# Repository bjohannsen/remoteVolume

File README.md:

# remoteVolume
An AVR-based IR controlled audio volume controller.
Primary purpose was to use active studio monitors with a TV without a fitting AV receiver.

# Features
* ATmega168 controller
* Volume controlling via <a href="http://www.ti.com/lit/ds/symlink/pga2311.pdf" target="_blank">TI PGA2311</a>
* Working with most IR protocols thanks to <a href="http://www.mikrocontroller.net/articles/IRMP" target="_blank">IRMP</a> library
* Two selectable input sources
* Switch output to control a subwoofer
* Display current volume by a ring of LEDs and a motorized pot.

#Caveats
* External power supply needed, for example <a href="http://www.meanwell.com/search/NET-35/NET-35-spec.pdf" target="_blank">Mean Well NET-35B</a>

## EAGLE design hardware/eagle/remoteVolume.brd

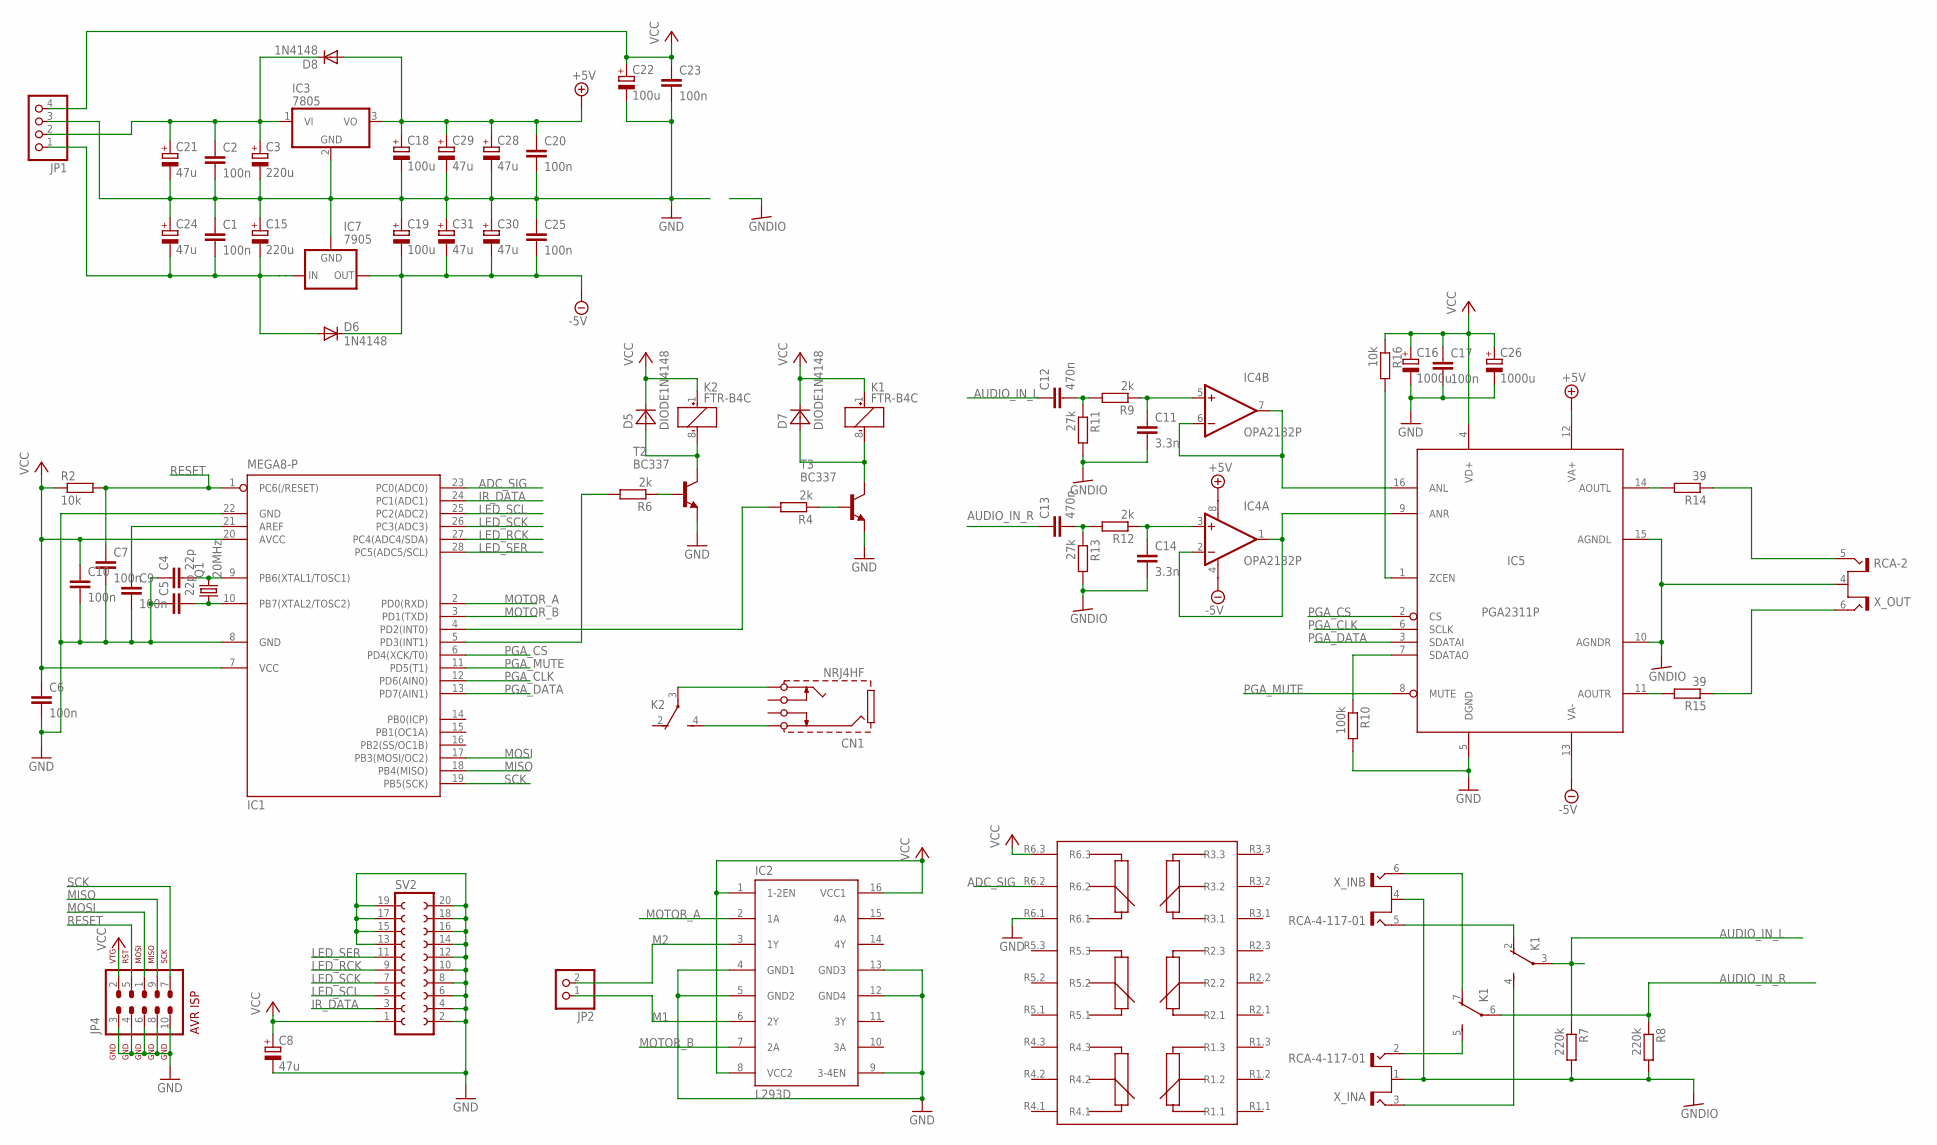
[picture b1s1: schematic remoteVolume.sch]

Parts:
C1, C2, C6, C7, C9, C10, C17, C20, C23, C25: 100n; C025-025X050
C3, C15: 220u; E2,5-6
C4, C5: 22p; C025-025X050
C8: 47u; E2,5-6
C11, C14: 3.3n; C050-055X075
C12, C13: 470n; C5B3.5
C16, C26: 1000u; E3,5-8
C18, C19, C22: 100u; E2,5-5
C21, C24, C28, C29, C30, C31: 47u; E2,5-5
CN1: NRJ4HF
D5, D7: DIODE1N4148; DO-35
D6, D8: 1N4148; DO35-7
IC1: MEGA8-P; DIL28-3
IC2: L293D; DIL16
IC3: 7805; TO220V
IC4: OPA2132P; DIL08
IC5: PGA2311P; DIL16
IC7: 7905; 79XXS
JP1: PINHD-1X4/90; 1X04/90
JP2: PINHD-1X2; 1X02
JP4: AVR-ISP-10
K1, K2: FTR-B4C
Q1: 20MHz; HC49/S
R2, R16: 10k; 0207/7
R4, R6, R9, R12: 2k; 0207/7
R7, R8: 220k; 0207/7
R10: 100k; 0207/7
R11, R13: 27k; 0207/7
R14, R15: 39; 0207/7
SV2: FE10-2W
T2, T3: BC337; TO92
U$1: RK16816MG
X_IN: RCA-4-117-01
X_OUT: RCA-2

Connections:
+5V: C18.+, C20.1, C28.+, C29.+, D8.A, IC3.3 (VO), IC4.8 (V+), IC5.12 (VA+)
-5V: C19.-, C25.2, C30.-, C31.-, D6.C, IC4.4 (V-), IC5.13 (VA-), IC7.OUT
ADC_SIG: IC1.23 (PC0(ADC0)), U$1.R6.2
AUDIO_IN_L: C12.1, K1.3, R7.1
AUDIO_IN_R: C13.1, K1.6, R8.1
GND: C1.1, C2.2, C3.-, C4.1, C5.1, C6.2, C7.2, C8.-, C9.2, C10.2, C15.+, C16.-, C17.2, C18.-, C19.+, C20.2, C21.-, C22.-, C23.2, C24.+, C25.1, C26.-, C28.-, C29.-, C30.+, C31.+, IC1.8 (GND), IC1.22 (GND), IC2.4 (GND1), IC2.5 (GND2), IC2.9 (3-4EN), IC2.12 (GND4), IC2.13 (GND3), IC3.2 (GND), IC5.5 (DGND), IC7.GND, JP1.3, JP4.3, JP4.4, JP4.6, JP4.8, JP4.10, R10.2, SV2.2, SV2.4, SV2.6, SV2.8, SV2.10, SV2.12, SV2.13, SV2.14, SV2.15, SV2.16, SV2.17, SV2.18, SV2.19, SV2.20, T2.1 (E), T3.1 (E), U$1.R6.1
GNDIO: C11.2, C14.2, IC5.10 (AGNDR), IC5.15 (AGNDL), R7.2, R8.2, R11.2, R13.2, X_IN.1 (S), X_IN.4 (S), X_OUT.4 (S)
IR_DATA: IC1.24 (PC1(ADC1)), SV2.3
LED_RCK: IC1.27 (PC4(ADC4/SDA)), SV2.9
LED_SCK: IC1.26 (PC3(ADC3)), SV2.7
LED_SCL: IC1.25 (PC2(ADC2)), SV2.5
LED_SER: IC1.28 (PC5(ADC5/SCL)), SV2.11
M1: IC2.6 (2Y), JP2.1
M2: IC2.3 (1Y), JP2.2
MISO: IC1.18 (PB4(MISO)), JP4.9
MOSI: IC1.17 (PB3(MOSI/OC2)), JP4.1
MOTOR_A: IC1.2 (PD0(RXD)), IC2.2 (1A)
MOTOR_B: IC1.3 (PD1(TXD)), IC2.7 (2A)
unnamed: CN1.SLEEVE, K2.4 (S)
unnamed: IC4.1 (OUT), IC4.2 (-IN), IC5.9 (ANR)
unnamed: C2.1, C3.+, C21.+, D8.C, IC3.1 (VI), JP1.2
unnamed: C1.2, C15.-, C24.-, D6.A, IC7.IN, JP1.1
unnamed: K1.5 (S), X_IN.2 (T1)
unnamed: D7.+, K1.8 (-), T3.3 (C)
unnamed: C4.2, IC1.9 (PB6(XTAL1/TOSC1)), Q1.2
unnamed: C5.2, IC1.10 (PB7(XTAL2/TOSC2)), Q1.1
unnamed: R4.1, T3.2 (B)
unnamed: IC1.4 (PD2(INT0)), R4.2
unnamed: K1.7 (O), X_IN.6 (T2)
unnamed: IC1.5 (PD3(INT1)), R6.2
unnamed: K1.2 (O), X_IN.5 (T1)
unnamed: R6.1, T2.2 (B)
unnamed: K1.4 (S), X_IN.3 (T2)
unnamed: D5.+, K2.8 (-), T2.3 (C)
unnamed: CN1.TIP, K2.3
unnamed: C9.1, IC1.21 (AREF)
unnamed: IC4.6 (-IN), IC4.7 (OUT), IC5.16 (ANL)
unnamed: C12.2, R9.2, R11.1
unnamed: C11.1, IC4.5 (+IN), R9.1
unnamed: C14.1, IC4.3 (+IN), R12.1
unnamed: R14.1, X_OUT.5 (T1)
unnamed: R15.1, X_OUT.6 (T2)
unnamed: C13.2, R12.2, R13.1
unnamed: IC5.7 (SDATAO), R10.1
unnamed: IC5.14 (AOUTL), R14.2
unnamed: IC5.11 (AOUTR), R15.2
unnamed: IC5.1 (ZCEN), R16.2
PGA_CLK: IC1.12 (PD6(AIN0)), IC5.6 (SCLK)
PGA_CS: IC1.6 (PD4(XCK/T0)), IC5.2 (CS)
PGA_DATA: IC1.13 (PD7(AIN1)), IC5.3 (SDATAI)
PGA_MUTE: IC1.11 (PD5(T1)), IC5.8 (MUTE)
RESET: C7.1, IC1.1 (PC6(/RESET)), JP4.5, R2.2
SCK: IC1.19 (PB5(SCK)), JP4.7
VCC: C6.1, C8.+, C10.1, C16.+, C17.1, C22.+, C23.1, C26.+, D5.-, D7.-, IC1.7 (VCC), IC1.20 (AVCC), IC2.1 (1-2EN), IC2.8 (VCC2), IC2.16 (VCC1), IC5.4 (VD+), JP1.4, JP4.2, K1.1 (+), K2.1 (+), R2.1, R16.1, SV2.1, U$1.R6.3

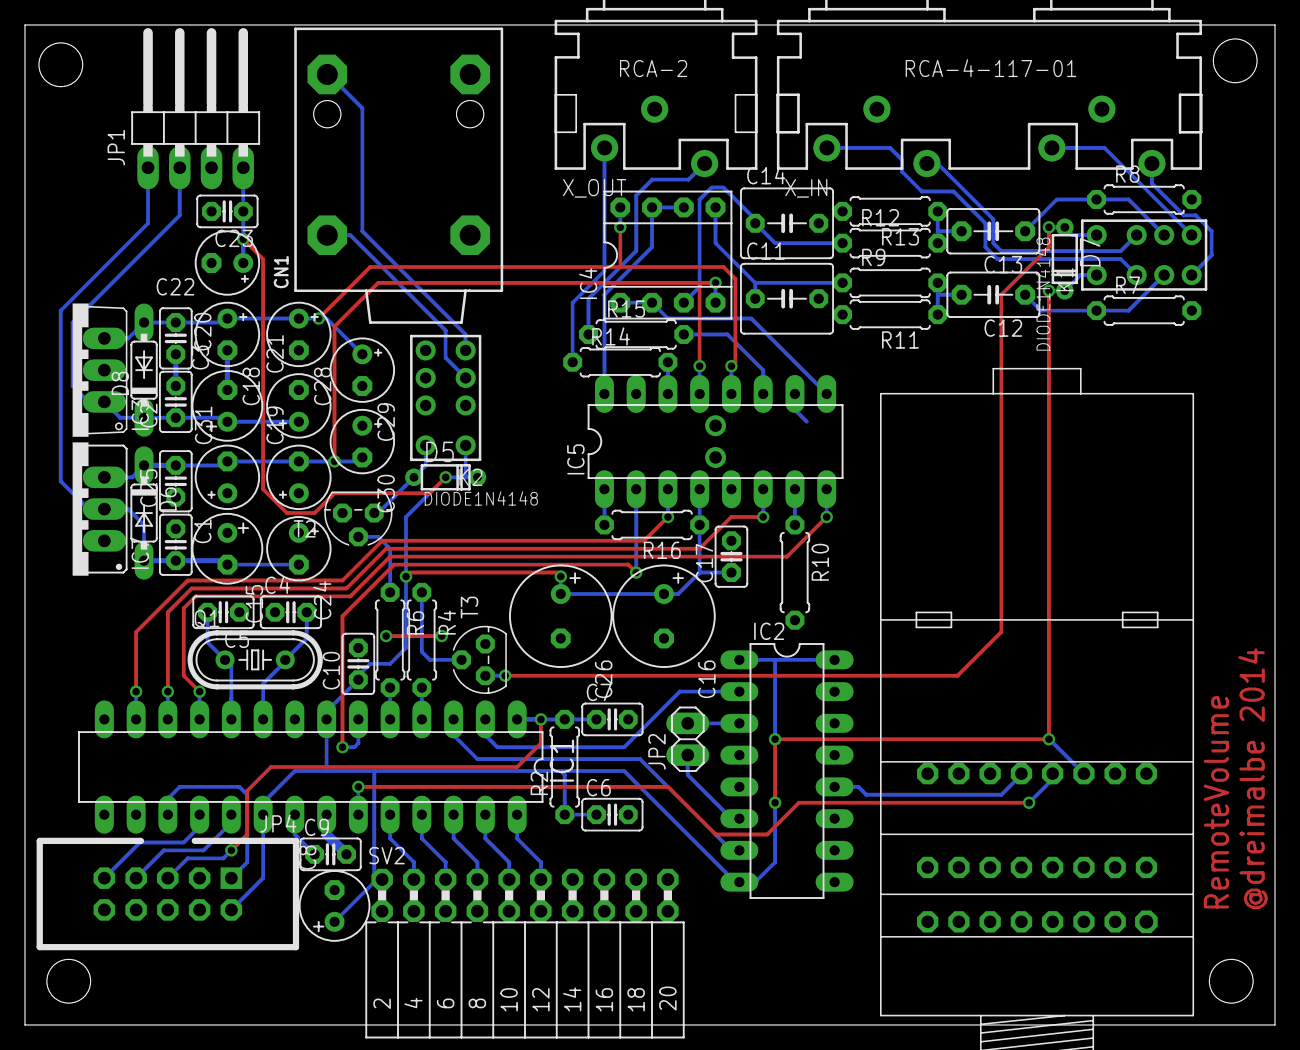
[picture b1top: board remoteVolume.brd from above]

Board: 2 copper layers, 99.8 x 79.8 mm, 66 parts (0 on the bottom side), 54 nets.

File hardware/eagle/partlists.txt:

Parts
Front Panel:
IC1      74HCT595N      DIL16    
IC2      74HCT595N      DIL16    
R1       1.5k           0207/7 
R2       1.5k           0207/7 
R3       1.5k           0207/7 
R4       1.5k           0207/7 
R5       1.5k           0207/7
R6       1.5k           0207/7
R7       1.5k           0207/7
R8       1.5k           0207/7
R9       1.5k           0207/7
R10      1.5k           0207/7
R11      1.5k           0207/7
R12      1.5k           0207/7
R13      1.5k           0207/7
R14      1.5k           0207/7
R15      1.5k           0207/7
R16      1.5k           0207/7
R17      100            0207/7
SV2      --             MA10-2
U$2      --		16x3mm LED low current
U$3      TSOP1738       TSOP17XX

Main:
C1       100n           C025-025X050
C2       100n           C025-025X050
C3       220u           E2,5-6      
C4       22p            C025-025X050
C5       22p            C025-025X050
C6       100n           C025-025X050
C7       100n           C025-025X050
C8       47u            E2,5-6      
C9       100n           C025-025X050
C10      100n           C025-025X050
C11      3.3n           C050-055X075
C12      470n           C5B3.5      
C13      470n           C5B3.5      
C14      3.3n           C050-055X075
C15      220u           E2,5-6      
C16      1000u          E3,5-8      
C17      100n           C025-025X050
C18      100u           E2,5-5      
C19      100u           E2,5-5      
C20      100n           C025-025X050
C21      47u            E2,5-5      
C22      100u           E2,5-5      
C23      100n           C025-025X050
C24      47u            E2,5-5      
C25      100n           C025-025X050
C26      1000u          E3,5-8      
C28      47u            E2,5-5      
C29      47u            E2,5-5      
C30      47u            E2,5-5      
C31      47u            E2,5-5      
CN1      NRJ4HF         NRJ4HF      
D5       1N4148    	DO-35       
D6       1N4148         DO-35
D7       1N4148    	DO-35       
D8       1N4148         DO35
IC1      MEGA168-P	DIL28-3     
IC2      L293D          DIL16       
IC3      7805           TO220V      
IC4      OPA2132P       DIL08       
IC5      PGA2311P       DIL16       
IC7      7905           TO220V      
JP1      --             1X04/90     
JP4      --	    	AVR-ISP-10  
K1       --		FTR-B4C
K2       --		FTR-B4C
Q1       20MHz          HC49/S      
R2       10k            0207/7      
R4       2k             0207/7      
R6       2k             0207/7      
R7       220k           0207/7      
R8       220k           0207/7      
R9       2k             0207/7      
R10      100k           0207/7      
R11      27k            0207/7      
R12      2k             0207/7     
R13      27k            0207/7     
R14      39             0207/7     
R15      39             0207/7     
R16      10k            0207/7     
SV2      --             FE10-2W    
T2       BC337          TO92       
T3       BC337          TO92       
U$1      --		RK16816MG  
X_IN     --		RCA-4-117-01
X_OUT    --		RCA-2

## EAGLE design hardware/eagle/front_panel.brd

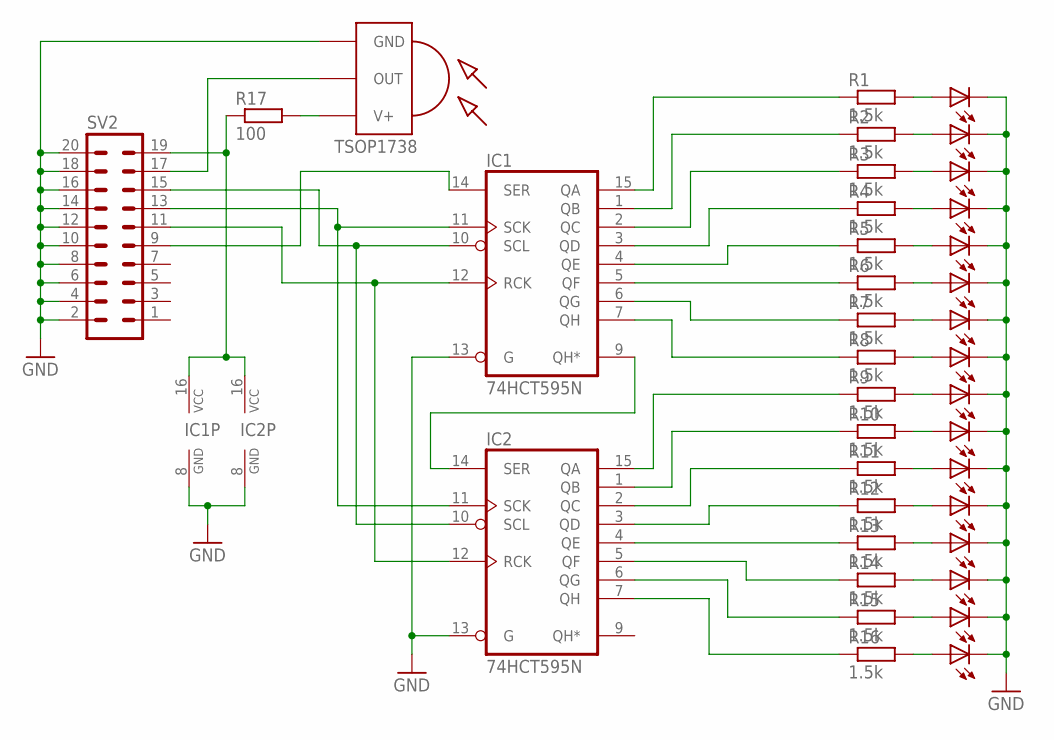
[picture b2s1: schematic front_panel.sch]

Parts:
IC1, IC2: 74HCT595N; DIL16
R1, R2, R3, R4, R5, R6, R7, R8, R9, R10, R11, R12, R13, R14, R15, R16: 1.5k; 0207/7
R17: 100; 0207/7
SV2: MA10-2
U$2: LED_RING_16; POTI_LED_RING16
U$3: TSOP1738; TSOP17XX

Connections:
GND: IC1.8 (GND), IC1.13 (G), IC2.8 (GND), IC2.13 (G), SV2.2, SV2.4, SV2.6, SV2.8, SV2.10, SV2.12, SV2.14, SV2.16, SV2.18, SV2.20, U$2.K0, U$2.K1, U$2.K2, U$2.K3, U$2.K4, U$2.K5, U$2.K6, U$2.K7, U$2.K8, U$2.K9, U$2.K10, U$2.K11, U$2.K12, U$2.K13, U$2.K14, U$2.K15, U$3.GND
unnamed: IC1.9 (QH*), IC2.14 (SER)
unnamed: R9.2, U$2.A8
unnamed: IC1.11 (SCK), IC2.11 (SCK), SV2.13
unnamed: IC1.10 (SCL), IC2.10 (SCL), SV2.15
unnamed: IC1.12 (RCK), IC2.12 (RCK), SV2.11
unnamed: IC1.14 (SER), SV2.9
unnamed: R1.2, U$2.A0
unnamed: R2.2, U$2.A1
unnamed: R3.2, U$2.A2
unnamed: R4.2, U$2.A3
unnamed: R5.2, U$2.A4
unnamed: R6.2, U$2.A5
unnamed: R7.2, U$2.A6
unnamed: R8.2, U$2.A7
unnamed: R10.2, U$2.A9
unnamed: R11.2, U$2.A10
unnamed: R12.2, U$2.A11
unnamed: R13.2, U$2.A12
unnamed: R14.2, U$2.A13
unnamed: R15.2, U$2.A14
unnamed: R16.2, U$2.A15
unnamed: IC1.15 (QA), R1.1
unnamed: IC1.1 (QB), R2.1
unnamed: IC1.2 (QC), R3.1
unnamed: IC1.3 (QD), R4.1
unnamed: IC1.7 (QH), R8.1
unnamed: IC1.6 (QG), R7.1
unnamed: IC1.5 (QF), R6.1
unnamed: IC1.4 (QE), R5.1
unnamed: IC2.15 (QA), R9.1
unnamed: IC2.1 (QB), R10.1
unnamed: IC2.2 (QC), R11.1
unnamed: IC2.3 (QD), R12.1
unnamed: IC2.7 (QH), R16.1
unnamed: IC2.6 (QG), R15.1
unnamed: IC2.5 (QF), R14.1
unnamed: IC2.4 (QE), R13.1
unnamed: SV2.17, U$3.OUT
unnamed: R17.2, U$3.V+
unnamed: IC1.16 (VCC), IC2.16 (VCC), R17.1, SV2.19

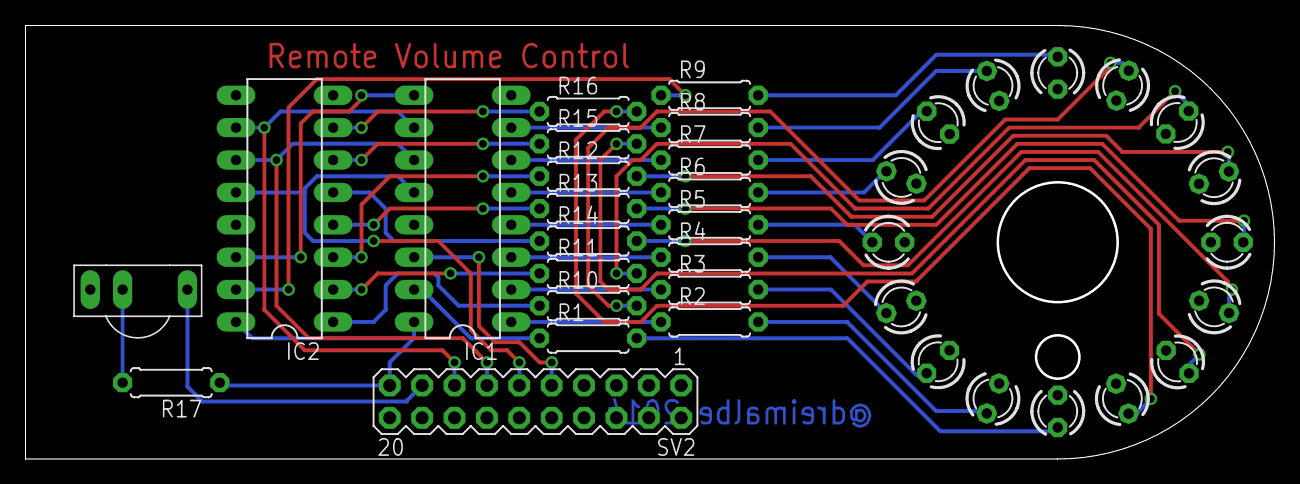
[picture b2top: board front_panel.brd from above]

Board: 2 copper layers, 97.8 x 33.8 mm, 22 parts (0 on the bottom side), 41 nets.

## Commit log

2015-03-30 Initial commit of project.
2015-03-30 Cleaned eclipse project files.
2015-03-31 Refactored motor pot logic to own source file.
2015-03-31 Refactored ir receiving handling.
2015-03-31 Refactored IRMP handling to separat file.
2015-03-31 Refactored relay controlling.
2015-04-01 Added hardware shematics and layouts.
2015-04-01 Reorganized project structure.
2015-04-01 Added more infos to readme.
2017-05-18 Added makeup gain for second source. Switch source on remote power button.

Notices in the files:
parts and their libraries:
audio: Copyright (C) 2008, Bob Starr
